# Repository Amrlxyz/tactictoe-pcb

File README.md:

# Tactic-toe PCB Design

## Project Details

**Tactic-toe Overview:** [amierulhakeem.dev/projects/tactictoe-overview/](https://amierulhakeem.dev/projects/tactictoe-overview/)

**Hardware Design:** [amierulhakeem.dev/projects/tactictoe-hardware/](https://amierulhakeem.dev/projects/tactictoe-hardware/)

Fully designed in **Kicad 9.0**

## PDF Exports

### [Schematic (v2)](/docs/schematic-v2.pdf)

### [PCB Layout (v2)](/docs/layout-v2.pdf)

### [Copper Layers (v2)](/docs/copper-layers-v2.pdf)

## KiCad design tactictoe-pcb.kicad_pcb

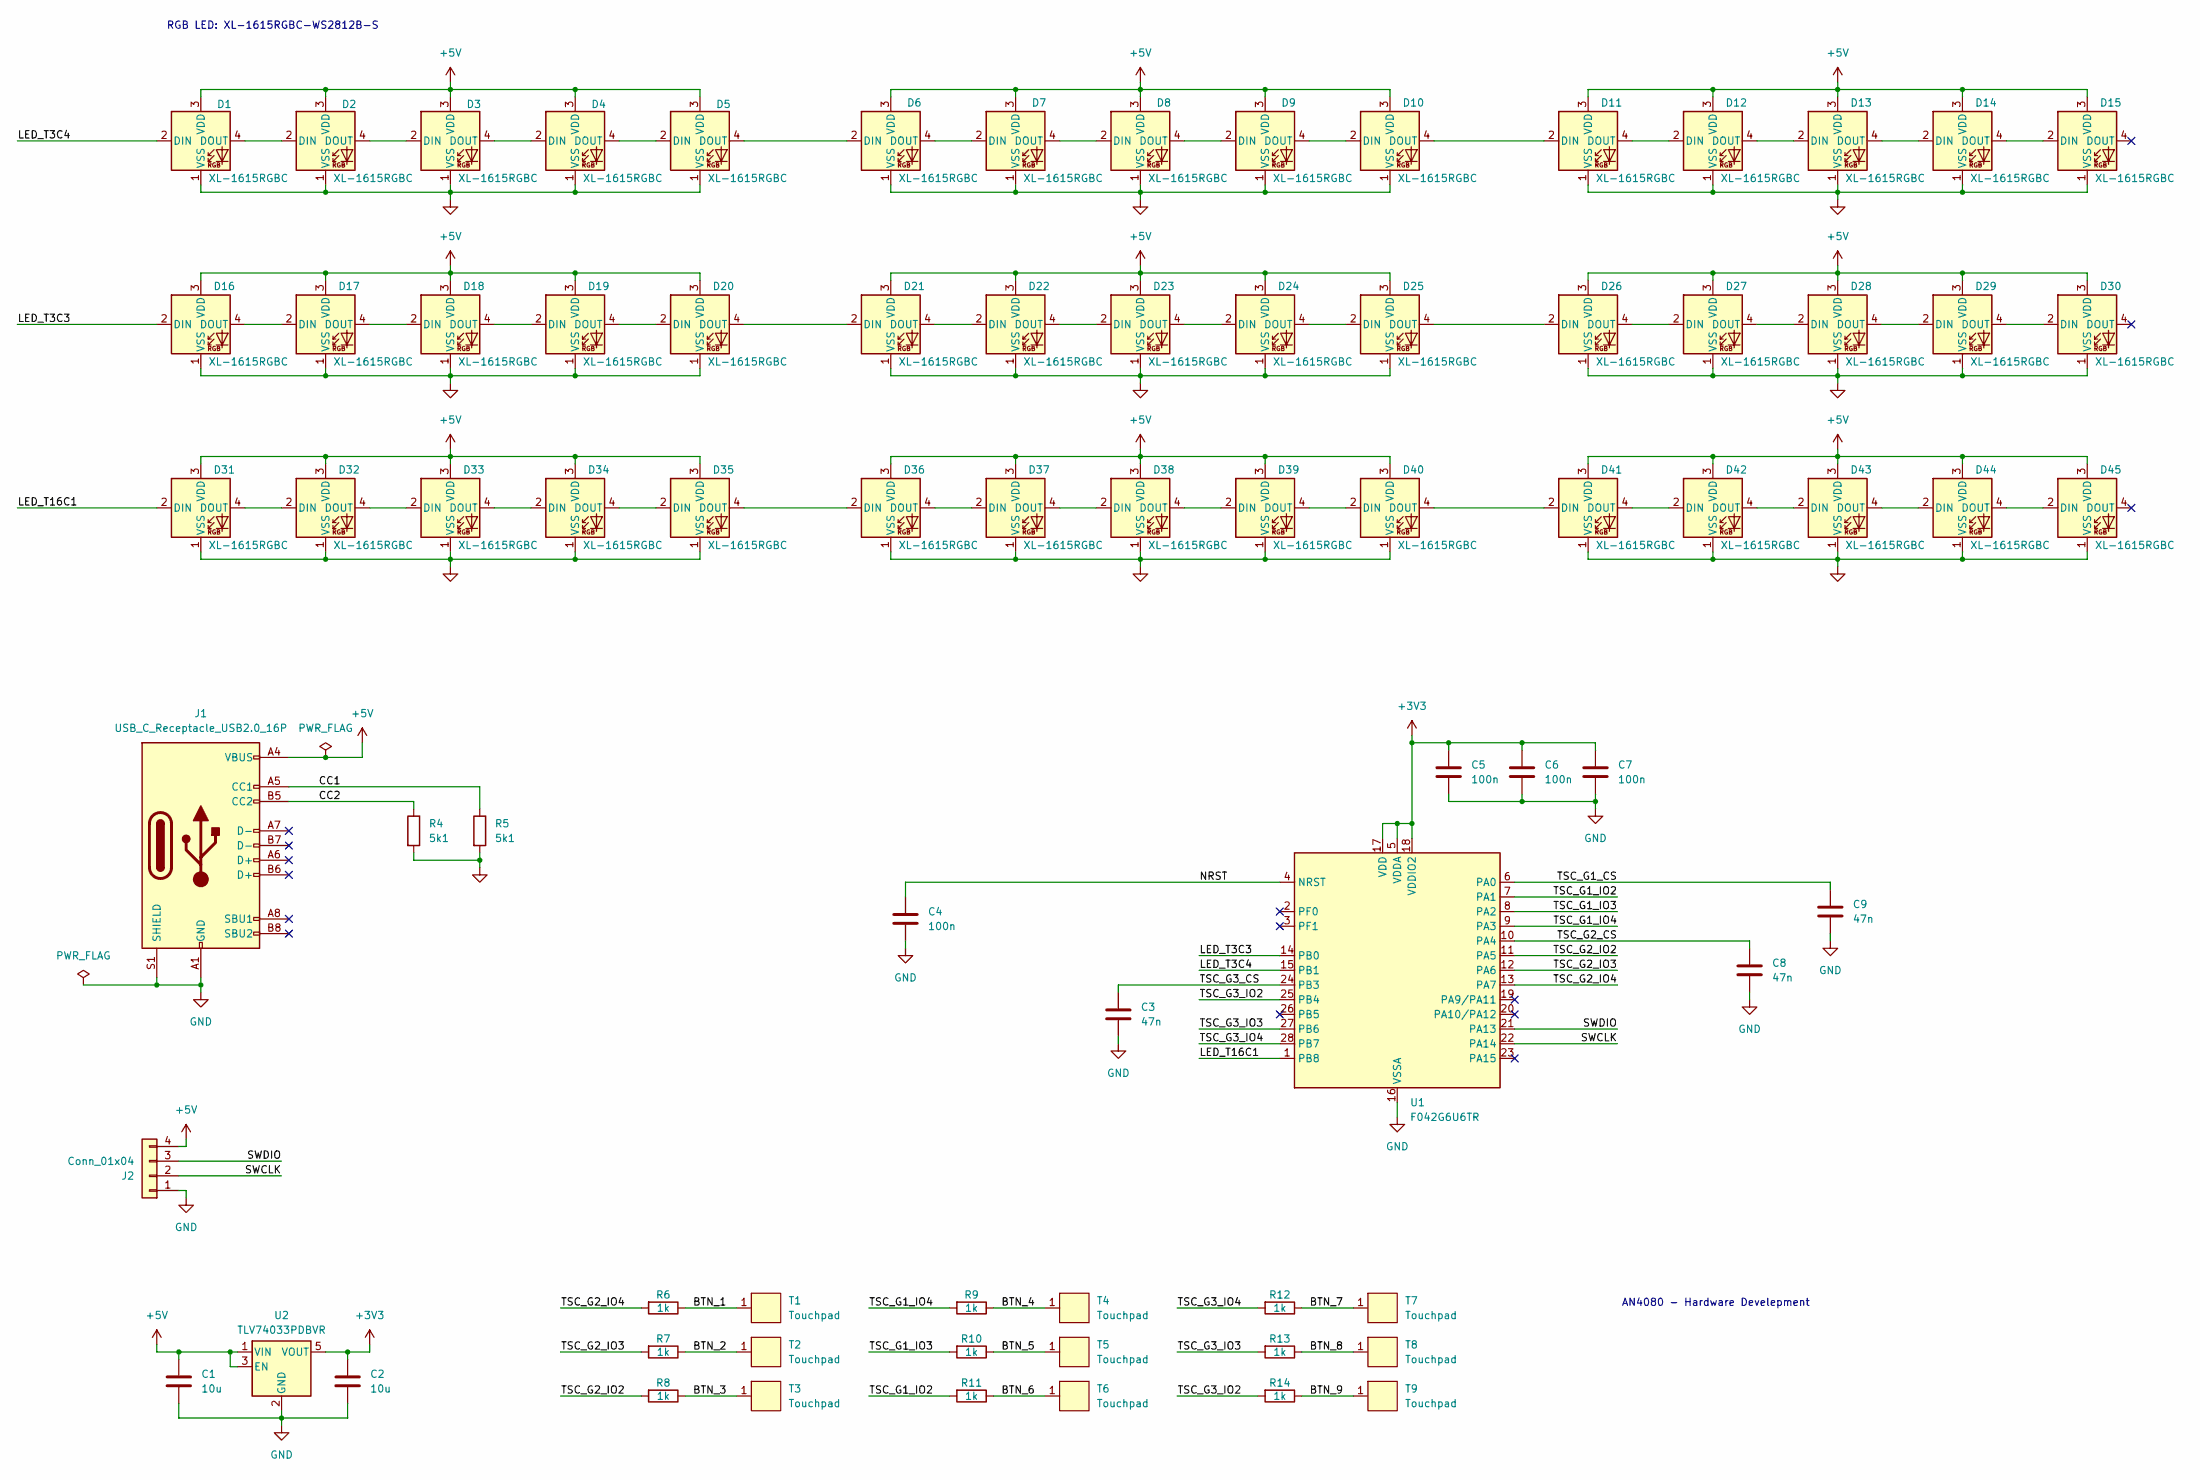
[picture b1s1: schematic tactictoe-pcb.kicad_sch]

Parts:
C1, C2: 10u; C_0603_1608Metric
C3, C8, C9: 47n; C_0603_1608Metric
C4, C5, C6, C7: 100n; C_0603_1608Metric
D1, D2, D3, D4, D5, D6, D7, D8, D9, D10, D11, D12, D13, D14, D15, D16, D17, D18, D19, D20, D21, D22, D23, D24, D25, D26, D27, D28, D29, D30, D31, D32, D33, D34, D35, D36, D37, D38, D39, D40, D41, D42, D43, D44, D45: XL-1615RGBC; XL-1615RGBC-WS2812B-S
J1: USB_C_Receptacle_USB2.0_16P; USB_C_Receptacle_TYPE-C-16P-CB1-6-073
J2: Conn_01x04; tactictoe-sw-pins
R4, R5: 5k1; R_0603_1608Metric
R6, R7, R8, R9, R10, R11, R12, R13, R14: 1k; R_0603_1608Metric
T1, T2, T3, T4, T5, T6, T7, T8, T9: Touchpad; Touch-pad_XL-1615
U1: F042G6U6TR; QFN-28_4x4mm_P0.5mm
U2: TLV74033PDBVR; SOT-23-5

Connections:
+3V3: C2.1, C5.1, C6.1, C7.1, U1.5 (VDDA), U1.17 (VDD), U1.18 (VDDIO2), U2.5 (VOUT)
+5V: C1.1, D1.3 (VDD), D2.3 (VDD), D3.3 (VDD), D4.3 (VDD), D5.3 (VDD), D6.3 (VDD), D7.3 (VDD), D8.3 (VDD), D9.3 (VDD), D10.3 (VDD), D11.3 (VDD), D12.3 (VDD), D13.3 (VDD), D14.3 (VDD), D15.3 (VDD), D16.3 (VDD), D17.3 (VDD), D18.3 (VDD), D19.3 (VDD), D20.3 (VDD), D21.3 (VDD), D22.3 (VDD), D23.3 (VDD), D24.3 (VDD), D25.3 (VDD), D26.3 (VDD), D27.3 (VDD), D28.3 (VDD), D29.3 (VDD), D30.3 (VDD), D31.3 (VDD), D32.3 (VDD), D33.3 (VDD), D34.3 (VDD), D35.3 (VDD), D36.3 (VDD), D37.3 (VDD), D38.3 (VDD), D39.3 (VDD), D40.3 (VDD), D41.3 (VDD), D42.3 (VDD), D43.3 (VDD), D44.3 (VDD), D45.3 (VDD), J1.A4 (VBUS), J1.A9 (VBUS), J1.B4 (VBUS), J1.B9 (VBUS), J2.4, U2.1 (VIN), U2.3 (EN)
/BTN_1: R6.1, T1.1
/BTN_2: R7.1, T2.1
/BTN_3: R8.1, T3.1
/BTN_4: R9.1, T4.1
/BTN_5: R10.1, T5.1
/BTN_6: R11.1, T6.1
/BTN_7: R12.1, T7.1
/BTN_8: R13.1, T8.1
/BTN_9: R14.1, T9.1
/CC1: J1.A5 (CC1), R5.1
/CC2: J1.B5 (CC2), R4.1
/LED_T3C3: D16.2 (DIN), U1.14 (PB0)
/LED_T3C4: D1.2 (DIN), U1.15 (PB1)
/LED_T16C1: D31.2 (DIN), U1.1 (PB8)
/NRST: C4.1, U1.4 (NRST)
/SWCLK: J2.2, U1.22 (PA14)
/SWDIO: J2.3, U1.21 (PA13)
/TSC_G1_CS: C9.1, U1.6 (PA0)
/TSC_G1_IO2: R11.2, U1.7 (PA1)
/TSC_G1_IO3: R10.2, U1.8 (PA2)
/TSC_G1_IO4: R9.2, U1.9 (PA3)
/TSC_G2_CS: C8.1, U1.10 (PA4)
/TSC_G2_IO2: R8.2, U1.11 (PA5)
/TSC_G2_IO3: R7.2, U1.12 (PA6)
/TSC_G2_IO4: R6.2, U1.13 (PA7)
/TSC_G3_CS: C3.1, U1.24 (PB3)
/TSC_G3_IO2: R14.2, U1.25 (PB4)
/TSC_G3_IO3: R13.2, U1.27 (PB6)
/TSC_G3_IO4: R12.2, U1.28 (PB7)
GND: C1.2, C2.2, C3.2, C4.2, C5.2, C6.2, C7.2, C8.2, C9.2, D1.1 (VSS), D2.1 (VSS), D3.1 (VSS), D4.1 (VSS), D5.1 (VSS), D6.1 (VSS), D7.1 (VSS), D8.1 (VSS), D9.1 (VSS), D10.1 (VSS), D11.1 (VSS), D12.1 (VSS), D13.1 (VSS), D14.1 (VSS), D15.1 (VSS), D16.1 (VSS), D17.1 (VSS), D18.1 (VSS), D19.1 (VSS), D20.1 (VSS), D21.1 (VSS), D22.1 (VSS), D23.1 (VSS), D24.1 (VSS), D25.1 (VSS), D26.1 (VSS), D27.1 (VSS), D28.1 (VSS), D29.1 (VSS), D30.1 (VSS), D31.1 (VSS), D32.1 (VSS), D33.1 (VSS), D34.1 (VSS), D35.1 (VSS), D36.1 (VSS), D37.1 (VSS), D38.1 (VSS), D39.1 (VSS), D40.1 (VSS), D41.1 (VSS), D42.1 (VSS), D43.1 (VSS), D44.1 (VSS), D45.1 (VSS), J1.A1 (GND), J1.A12 (GND), J1.B1 (GND), J1.B12 (GND), J1.S1 (SHIELD), J2.1, R4.2, R5.2, U1.16 (VSSA), U2.2 (GND)
unnamed: D1.4 (DOUT), D2.2 (DIN)
unnamed: D2.4 (DOUT), D3.2 (DIN)
unnamed: D3.4 (DOUT), D4.2 (DIN)
unnamed: D4.4 (DOUT), D5.2 (DIN)
unnamed: D5.4 (DOUT), D6.2 (DIN)
unnamed: D6.4 (DOUT), D7.2 (DIN)
unnamed: D7.4 (DOUT), D8.2 (DIN)
unnamed: D8.4 (DOUT), D9.2 (DIN)
unnamed: D9.4 (DOUT), D10.2 (DIN)
unnamed: D10.4 (DOUT), D11.2 (DIN)
unnamed: D11.4 (DOUT), D12.2 (DIN)
unnamed: D12.4 (DOUT), D13.2 (DIN)
unnamed: D13.4 (DOUT), D14.2 (DIN)
unnamed: D14.4 (DOUT), D15.2 (DIN)
unnamed: D16.4 (DOUT), D17.2 (DIN)
unnamed: D17.4 (DOUT), D18.2 (DIN)
unnamed: D18.4 (DOUT), D19.2 (DIN)
unnamed: D19.4 (DOUT), D20.2 (DIN)
unnamed: D20.4 (DOUT), D21.2 (DIN)
unnamed: D21.4 (DOUT), D22.2 (DIN)
unnamed: D22.4 (DOUT), D23.2 (DIN)
unnamed: D23.4 (DOUT), D24.2 (DIN)
unnamed: D24.4 (DOUT), D25.2 (DIN)
unnamed: D25.4 (DOUT), D26.2 (DIN)
unnamed: D26.4 (DOUT), D27.2 (DIN)
unnamed: D27.4 (DOUT), D28.2 (DIN)
unnamed: D28.4 (DOUT), D29.2 (DIN)
unnamed: D29.4 (DOUT), D30.2 (DIN)
unnamed: D31.4 (DOUT), D32.2 (DIN)
unnamed: D32.4 (DOUT), D33.2 (DIN)
unnamed: D33.4 (DOUT), D34.2 (DIN)
unnamed: D34.4 (DOUT), D35.2 (DIN)
unnamed: D35.4 (DOUT), D36.2 (DIN)
unnamed: D36.4 (DOUT), D37.2 (DIN)
unnamed: D37.4 (DOUT), D38.2 (DIN)
unnamed: D38.4 (DOUT), D39.2 (DIN)
unnamed: D39.4 (DOUT), D40.2 (DIN)
unnamed: D40.4 (DOUT), D41.2 (DIN)
unnamed: D41.4 (DOUT), D42.2 (DIN)
unnamed: D42.4 (DOUT), D43.2 (DIN)
unnamed: D43.4 (DOUT), D44.2 (DIN)
unnamed: D44.4 (DOUT), D45.2 (DIN)

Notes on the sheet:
RGB LED: XL-1615RGBC-WS2812B-S
AN4080 - Hardware Develepment

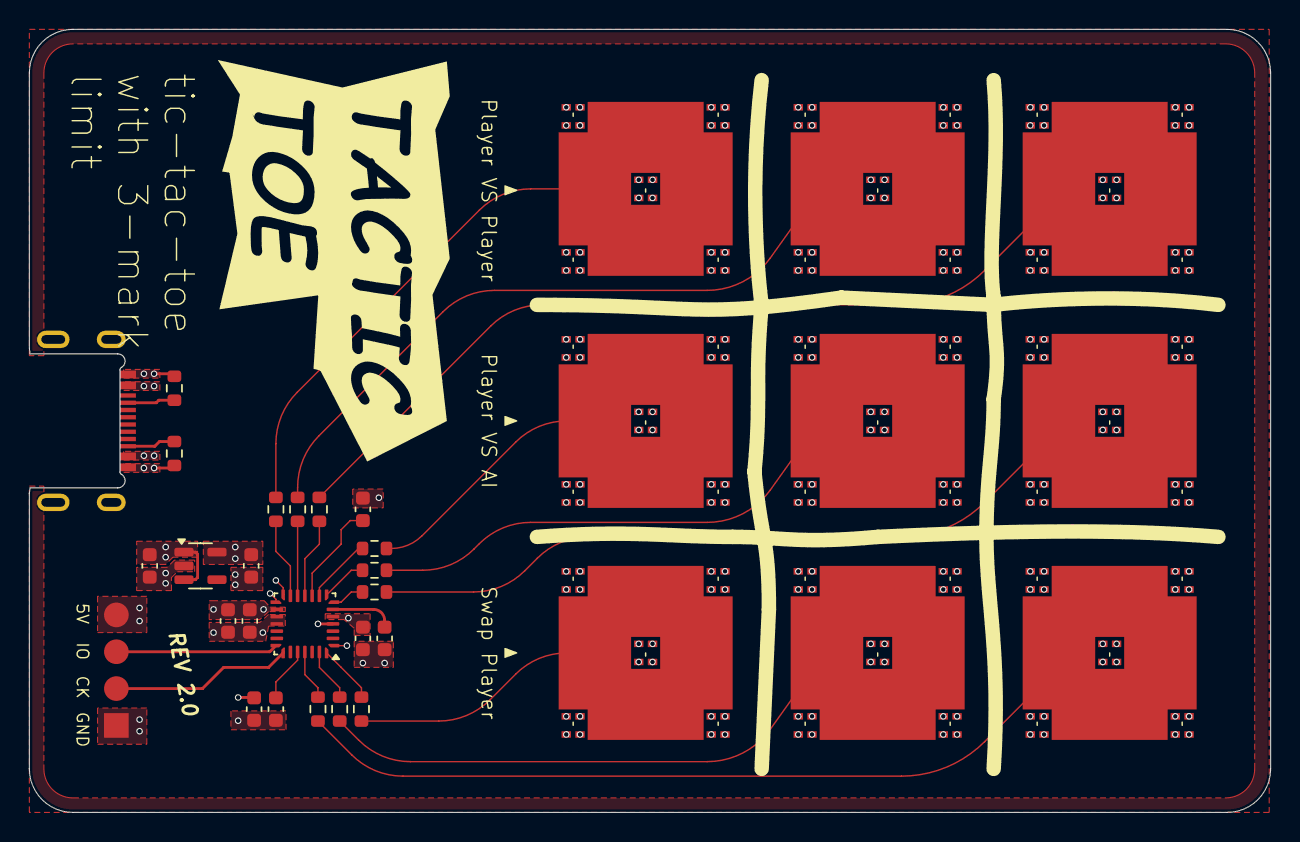
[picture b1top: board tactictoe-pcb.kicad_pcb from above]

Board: 4 copper layers, 85.6 x 54.0 mm, 78 parts (0 on the bottom side), 74 nets.

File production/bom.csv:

Designator,Footprint,Quantity,Value,LCSC Part #
"C1, C2",0603,2,10u,
"C3, C8, C9",0603,3,47n,
"C4, C5, C6, C7",0603,4,100n,
"D1, D10, D11, D12, D13, D14, D15, D16, D17, D18, D19, D2, D20, D21, D22, D23, D24, D25, D26, D27, D28, D29, D3, D30, D31, D32, D33, D34, D35, D36, D37, D38, D39, D4, D40, D41, D42, D43, D44, D45, D5, D6, D7, D8, D9",XL-1615RGBC-WS2812B-S,45,XL-1615RGBC,
J1,USB_C_Receptacle_TYPE-C-16P-CB1-6-073,1,USB_C_Receptacle_USB2.0_16P,
J2,tactictoe-sw-pins,1,Conn_01x04,
"R10, R11, R12, R13, R14, R6, R7, R8, R9",0603,9,1k,
"R4, R5",0603,2,5k1,
"T1, T2, T3, T4, T5, T6, T7, T8, T9",Touch-pad_XL-1615,9,Touchpad,
U1,QFN-28_4x4mm_P0.5mm,1,F042G6U6TR,
U2,SOT-23-5,1,TLV74033PDBVR,

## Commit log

2025-09-17 V1 PCB - First Commit
2025-09-17 v1 cleanup
2025-09-17 v1 production files cleanup
2025-09-17 v1 updated library names
2025-09-27 major v2 changes
2025-09-27 v2 fully routed
2025-09-28 silkscreen cleanup, v2 first gerber candidate
2026-02-01 fixed linkedin id typo
2026-02-02 Added Readme
